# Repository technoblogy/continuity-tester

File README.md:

Continuity Tester
=================
A simple continuity tester, based on an ATtiny85 and a piezo buzzer. For more information see http://www.technoblogy.com/show?1YON.

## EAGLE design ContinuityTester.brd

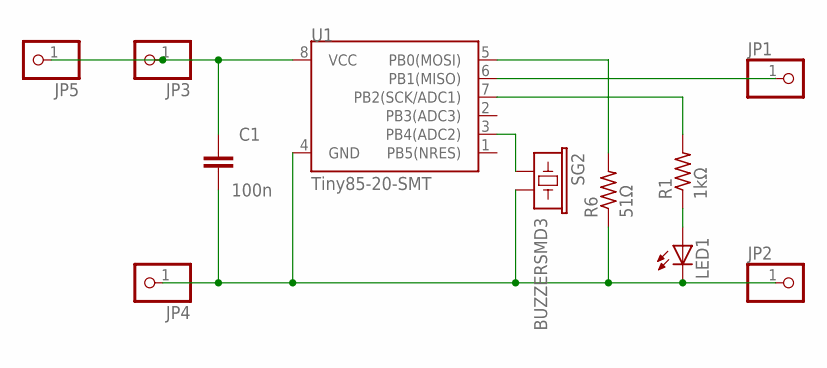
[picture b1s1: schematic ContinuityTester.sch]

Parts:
C1: 100n; 0603-CAP
JP1, JP2, JP3, JP4, JP5: PINHD-1X1CB; 1X01-CLEANBIG
LED1: LEDCHIPLED_0805; CHIPLED_0805
R1: 1kΩ; R0805
R6: 51Ω; R0805
SG2: BUZZERSMD3; BUZZER-CMT1102
U1: Tiny85-20-SMT; SO08-EIAJ

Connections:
unnamed: R6.2, U1.5 (PB0(MOSI))
unnamed: C1.2, JP2.1, JP4.1, LED1.C, R6.1, SG2.2, U1.4 (GND)
unnamed: SG2.1, U1.3 (PB4(ADC2))
unnamed: R1.2, U1.7 (PB2(SCK/ADC1))
unnamed: LED1.A, R1.1
unnamed: JP1.1, U1.6 (PB1(MISO))
unnamed: C1.1, JP3.1, JP5.1, U1.8 (VCC)

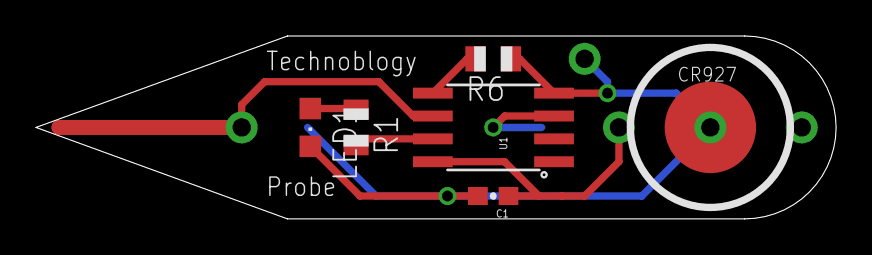
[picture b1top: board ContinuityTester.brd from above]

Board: 2 copper layers, 44.5 x 10.2 mm, 11 parts (1 on the bottom side), 7 nets.

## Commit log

2017-11-18 Version 1 - 18th November 2017

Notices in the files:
parts and their libraries:
SparkFun-DigitalIC: Licensing: Creative Commons ShareAlike 4.0 International - https://creativecommons.org/licenses/by-sa/4.0
SparkFun-Capacitors: Licensing: CC v3.0 Share-Alike You are welcome to use this library for commercial purposes.
